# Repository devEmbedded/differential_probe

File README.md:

Modular differential probe (DEDP-100)
=====================================

This repository contains the design files of a 100 MHz differential probe
for use with oscilloscopes. The design is modular and consists of a base
amplifier unit with exchangeable probe tip accessories. The accessory can
be chosen to fit the desired voltage range and connection type.

Currently this project is still in development. While the prototype revisions
work well, they are still being redesigned for improvements.

Files
=====

* [Design notes](design_notes/design_notes.md)
* [Schematics](diff_probe_amplifier/images/diff_probe_amplifier.pdf)
* [User manual](user_manual/DEDP-100_User_Manual.pdf)

License
=======

The design files in this repository are available under CC-BY-SA 3.0 license.

Commercial reproduction of this design is allowed, but the devEmbedded trademark
must not be used to advertise third-party products. Attribution must be included
in documentation or marketing materials.

Suggested format for attribution:

> This device is based on an open source design: https://github.com/devEmbedded/differential_probe

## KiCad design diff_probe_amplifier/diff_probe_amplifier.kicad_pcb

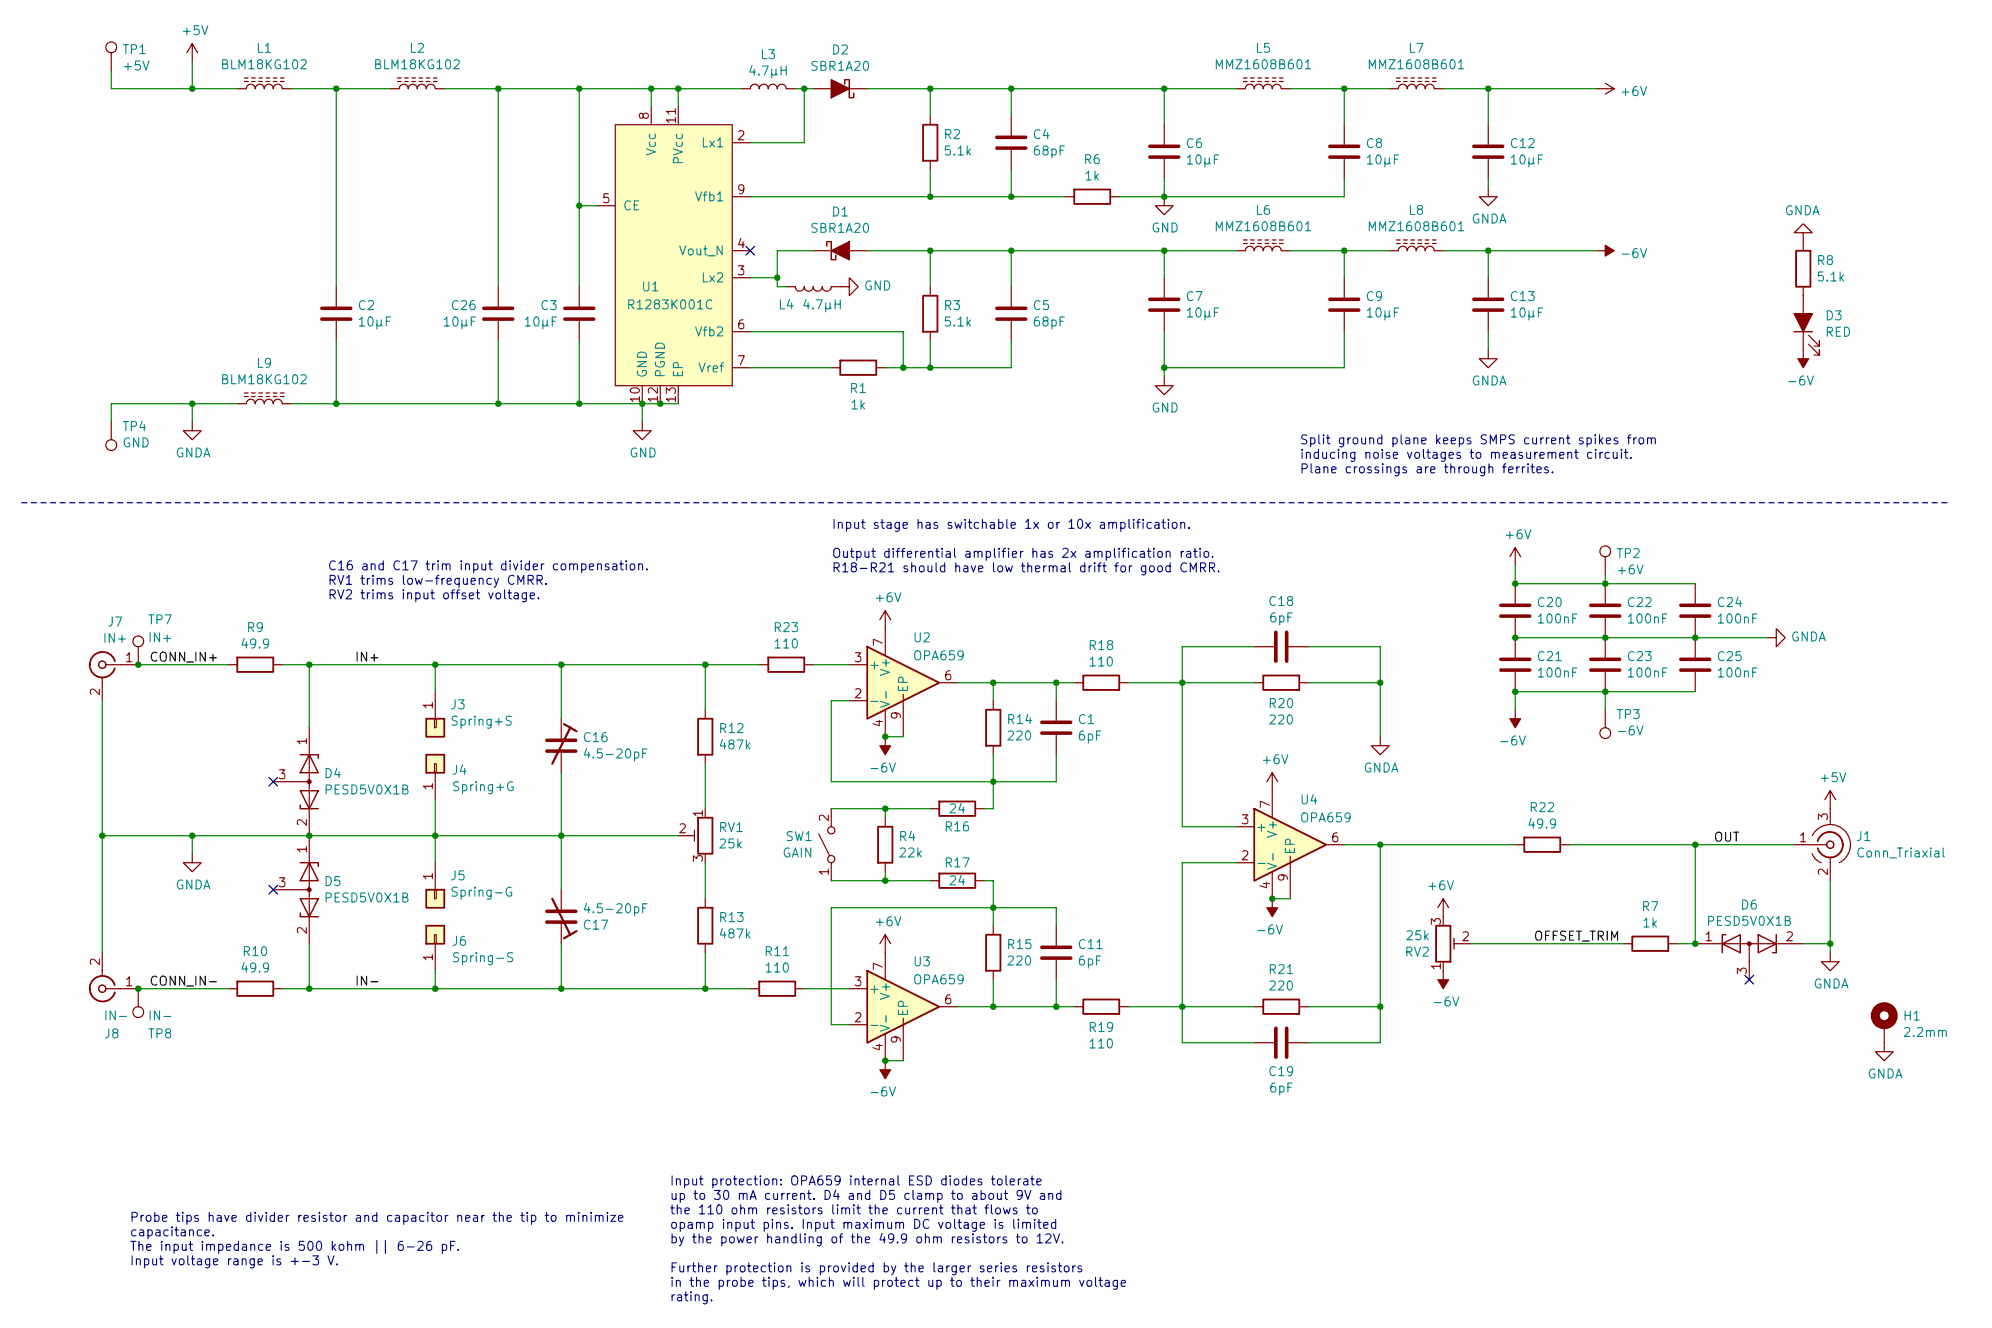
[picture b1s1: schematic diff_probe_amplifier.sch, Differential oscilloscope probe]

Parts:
C1, C11, C18, C19: 6pF; C_0603_1608Metric
C2, C3, C6, C7, C8, C9, C12, C13, C26: 10µF; C_0603_1608Metric; Mfg Part No 0603ZD106KAT2A
C4, C5: 68pF; C_0603_1608Metric; Mfg Part No CML0603C0G101JT50V
C16, C17: 4.5-20pF; C_Trimmer_Knowles_JZ_JR; Mfg Part No JZ200
C20, C21, C22, C23, C24, C25: 100nF; C_0603_1608Metric
D1, D2: SBR1A20; D_SOD-523; Mfg Part No SBR1A20
D3: RED; LED_0603_1608Metric; Mfg Part No QBLP601D-R
D4, D5, D6: PESD5V0X1B; SOT-23
H1: 2.2mm; MountingHole_2.2mm_M2_DIN965_Pad
J1: Conn_Triaxial; TRIAX_SOLDER
J3: Spring+S; TE_2306454_RIGHT; Mfg Part No 2306454-3
J4: Spring+G; TE_2306454_RIGHT; Mfg Part No 2306454-3
J5: Spring-G; TE_2306454_LEFT; Mfg Part No 2306454-3
J6: Spring-S; TE_2306454_LEFT; Mfg Part No 2306454-3
J7: IN+; MMCX_Molex_73415-0961_Horizontal_1.6mm-PCB; Mfg Part No 0734150963
J8: IN-; MMCX_Molex_73415-0961_Horizontal_1.6mm-PCB; Mfg Part No 0734150963
L1, L2, L9: BLM18KG102; L_0603_1608Metric
L3, L4: 4.7µH; L_0805_2012Metric_Pad1.15x1.40mm_HandSolder; Mfg Part No DFE201612E-4R7M=P2
L5, L6, L7, L8: MMZ1608B601; L_0603_1608Metric
R1, R6, R7: 1k; R_0603_1608Metric
R2, R3, R8: 5.1k; R_0603_1608Metric
R4: 22k; R_0603_1608Metric; Mfg Part No ERA-3AED111V
R9, R10, R22: 49.9; R_0603_1608Metric
R11, R23: 110; R_0603_1608Metric
R12, R13: 487k; R_0603_1608Metric
R14, R15, R20, R21: 220; R_0603_1608Metric; Mfg Part No ERA-3AED221V
R16, R17: 24; R_0603_1608Metric
R18, R19: 110; R_0603_1608Metric; Mfg Part No ERA-3AED111V
RV1, RV2: 25k; Potentiometer_Bourns_3314J_Vertical; Mfg Part No 3314J-1-253E
SW1: GAIN; JS202011JCQN; Mfg Part No JS202011JCQN
TP1: +5V; TestPoint_Pad_D2.5mm
TP2: +6V; TestPoint_Pad_D2.5mm
TP3: -6V; TestPoint_Pad_D2.5mm
TP4: GND; TestPoint_Pad_D2.5mm
TP7: IN+; TestPoint_Pad_D2.5mm
TP8: IN-; TestPoint_Pad_D2.5mm
U1: R1283K001C; DFN-12-1EP_3x4mm_P0.5mm_EP1.7x3.3mm
U2, U3, U4: OPA659; Texas_S-PVSON-N8_ThermalVias

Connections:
+5V: J1.3, L1.1, TP1.1
+6V: C12.1, C20.1, C22.1, C24.1, L7.2, RV2.3, TP2.1, U2.7 (V+), U3.7 (V+), U4.7 (V+)
-6V: C13.1, C21.2, C23.2, C25.2, D3.1 (K), L8.2, RV2.1, TP3.1, U2.4 (V-), U2.9 (EP), U3.4 (V-), U3.9 (EP), U4.4 (V-), U4.9 (EP)
/CONN_IN+: J7.1 (In), R9.2, TP7.1
/CONN_IN-: J8.1 (In), R10.2, TP8.1
/IN+: C16.1, D4.1 (K), J3.1, R9.1, R12.1, R23.2
/IN-: C17.1, D5.2 (K), J6.1, R10.1, R11.2, R13.1
/OFFSET_TRIM: R7.1, RV2.2
/OUT: D6.1 (K), J1.1 (In), R7.2, R22.1
GND: C2.2, C3.2, C6.2, C7.2, C8.2, C9.2, C26.2, L4.1, L9.2, R6.1, U1.10 (GND), U1.12 (PGND), U1.13 (EP)
GNDA: C12.2, C13.2, C16.2, C17.2, C18.1, C20.2, C21.1, C22.2, C23.1, C24.2, C25.1, D4.2 (K), D5.1 (K), D6.2 (K), H1.1, J1.2 (Ext), J4.1, J5.1, J7.2 (Ext), J8.2 (Ext), L9.1, R8.2, R20.2, RV1.2, TP4.1
unnamed: C1.1, R14.2, R16.1, U2.2 (-)
unnamed: C1.2, R14.1, R18.1, U2.6
unnamed: C2.1, L1.2, L2.1
unnamed: C4.1, C6.1, D2.1 (K), L5.1, R2.1
unnamed: C4.2, R2.2, R6.2, U1.9 (Vfb1)
unnamed: C5.1, C7.1, D1.2 (A), L6.1, R3.1
unnamed: C5.2, R1.1, R3.2, U1.6 (Vfb2)
unnamed: C8.1, L5.2, L7.1
unnamed: C9.1, L6.2, L8.1
unnamed: C11.1, R15.2, R19.1, U3.6
unnamed: C11.2, R15.1, R17.1, U3.2 (-)
unnamed: C18.2, R18.2, R20.1, U4.3 (+)
unnamed: C19.1, R21.2, R22.2, U4.6
unnamed: C19.2, R19.2, R21.1, U4.2 (-)
unnamed: C3.1, C26.1, L2.2, L3.1, U1.5 (CE), U1.8 (Vcc), U1.11 (PVcc)
unnamed: D1.1 (K), L4.2, U1.3 (Lx2)
unnamed: D2.2 (A), L3.2, U1.2 (Lx1)
unnamed: D3.2 (A), R8.1
unnamed: R1.2, U1.7 (Vref)
unnamed: R11.1, U3.3 (+)
unnamed: R12.2, RV1.1
unnamed: R13.2, RV1.3
unnamed: R4.1, R16.2, SW1.2 (B)
unnamed: R4.2, R17.2, SW1.1 (A)
unnamed: R23.1, U2.3 (+)

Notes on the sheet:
C16 and C17 trim input divider compensation. RV1 trims low-frequency CMRR. RV2 trims input offset voltage.
Input stage has switchable 1x or 10x amplification. Output differential amplifier has 2x amplification ratio. R18-R21 should have low thermal drift for good CMRR.
Probe tips have divider resistor and capacitor near the tip to minimize capacitance. The input impedance is 500 kohm || 6-26 pF. Input voltage range is +-3 V.
Input protection: OPA659 internal ESD diodes tolerate up to 30 mA current. D4 and D5 clamp to about 9V and the 110 ohm resistors limit the current that flows to opamp input pins. Input maximum DC voltage is limited by the power handling of the 49.9 ohm resistors to 12V. Further protection is provid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
Split ground plane keeps SMPS current spikes from inducing noise voltages to measurement circuit. Plane crossings are through ferrites.

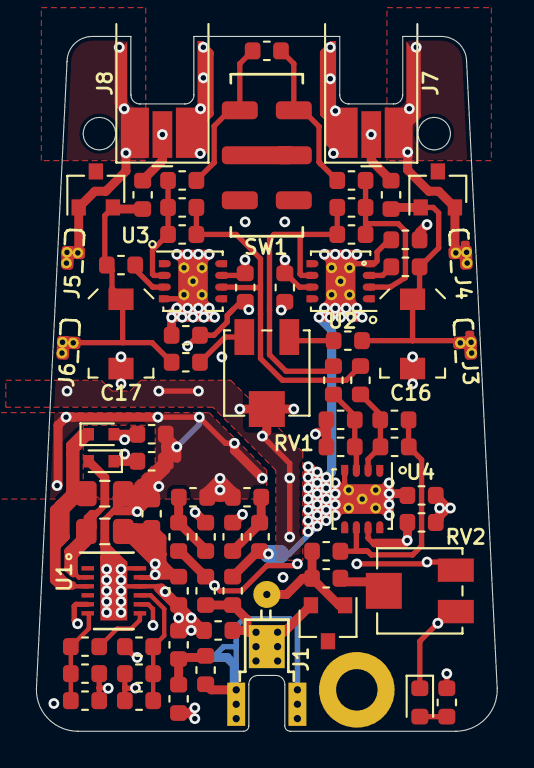
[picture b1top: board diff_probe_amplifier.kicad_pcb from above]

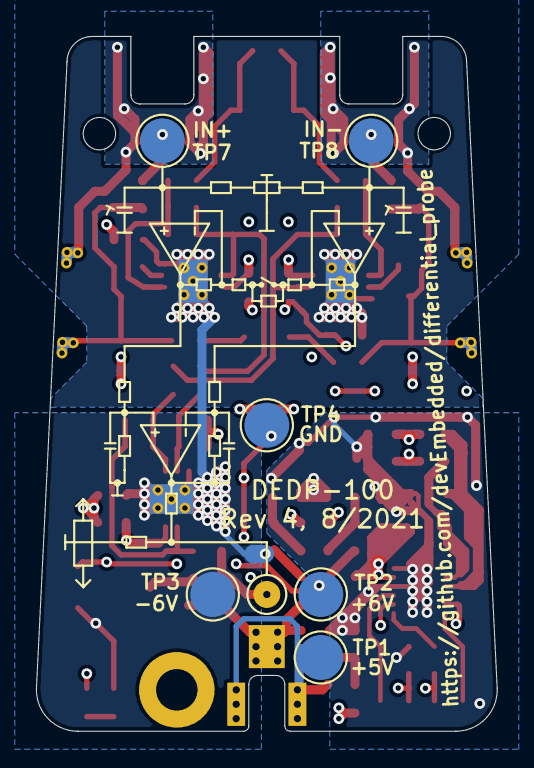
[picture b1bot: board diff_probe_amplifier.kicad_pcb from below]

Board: 4 copper layers, 25.6 x 38.6 mm, 83 parts (6 on the bottom side), 36 nets.

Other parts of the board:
H2, H2#2: HOLE_1.8mm

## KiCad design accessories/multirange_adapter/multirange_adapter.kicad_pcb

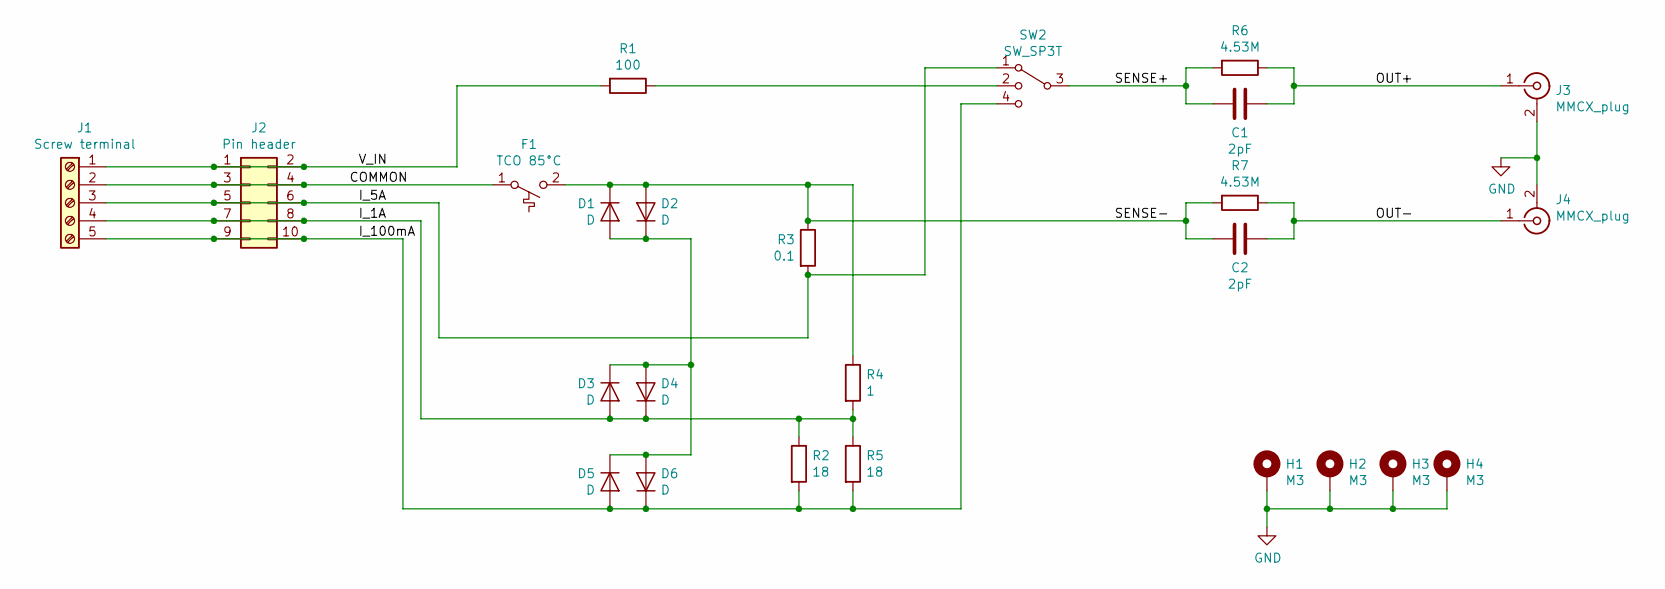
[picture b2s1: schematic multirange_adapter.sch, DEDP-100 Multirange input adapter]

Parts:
C1, C2: 2pF; C_0603_1608Metric
D1, D2, D3, D4, D5, D6: D; D_SMA
F1: TCO 85°C; SA82SB0
H1, H2, H3, H4: M3; MountingHole_3.2mm_M3_ISO14580_Pad
J1: Screw terminal; TerminalBlock_bornier-5_P5.08mm
J2: Pin header; PinHeader_2x05_P2.54mm_Vertical_SMD
J3, J4: MMCX_plug; MMCX_Molex_73415-0961_Horizontal_1.6mm-PCB
R1: 100; R_0603_1608Metric
R2, R5: 18; R_1206_3216Metric
R3: 0.1; R_2512_6332Metric
R4: 1; R_2512_6332Metric
R6, R7: 4.53M; R_0603_1608Metric
SW2: SW_SP3T; JS203011SCQN

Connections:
/COMMON: F1.1 (A), J1.2, J2.3, J2.4
/I_1A: D3.2 (A), D4.1 (K), J1.4, J2.7, J2.8, R2.1, R4.2, R5.1
/I_5A: J1.3, J2.5, J2.6, R3.2, SW2.1
/I_100mA: D5.2 (A), D6.1 (K), J1.5, J2.9, J2.10, R2.2, R5.2, SW2.4
/OUT+: C1.1, J3.1 (In), R6.1
/OUT-: C2.1, J4.1 (In), R7.1
/SENSE+: C1.2, R6.2, SW2.3
/SENSE-: C2.2, D1.1 (K), D2.2 (A), F1.2 (B), R3.1, R4.1, R7.2
/V_IN: J1.1, J2.1, J2.2, R1.2
GND: H1.1, H2.1, H3.1, H4.1, J3.2 (Ext), J4.2 (Ext)
unnamed: D1.2 (A), D2.1 (K), D3.1 (K), D4.2 (A), D5.1 (K), D6.2 (A)
unnamed: R1.1, SW2.2

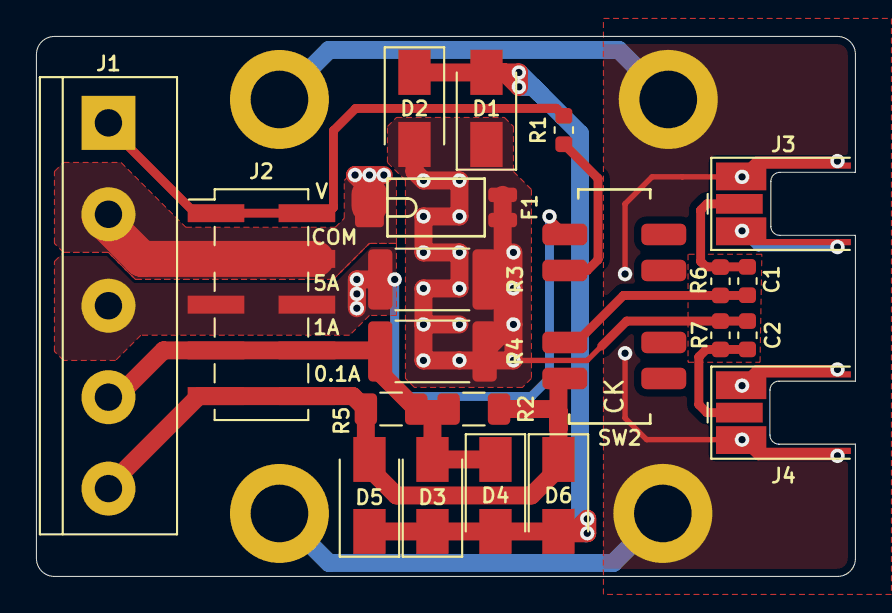
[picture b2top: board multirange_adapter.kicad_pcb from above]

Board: 2 copper layers, 45.5 x 30.0 mm, 25 parts (0 on the bottom side), 12 nets.

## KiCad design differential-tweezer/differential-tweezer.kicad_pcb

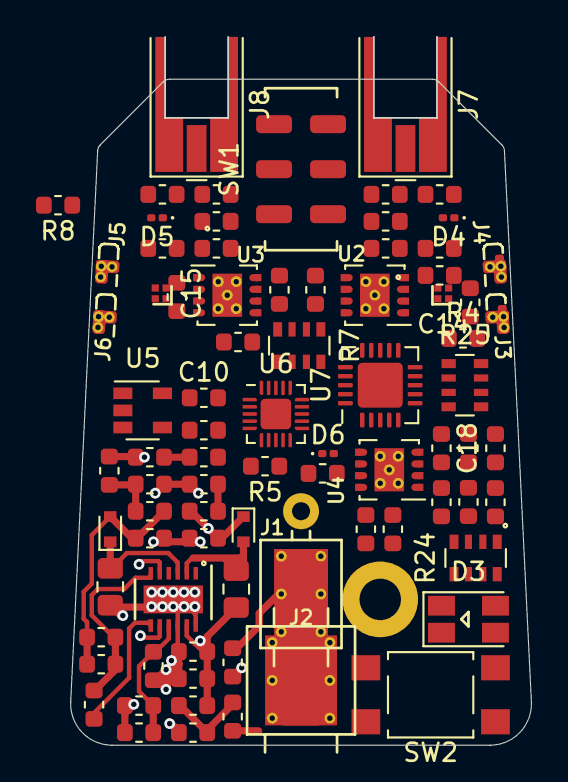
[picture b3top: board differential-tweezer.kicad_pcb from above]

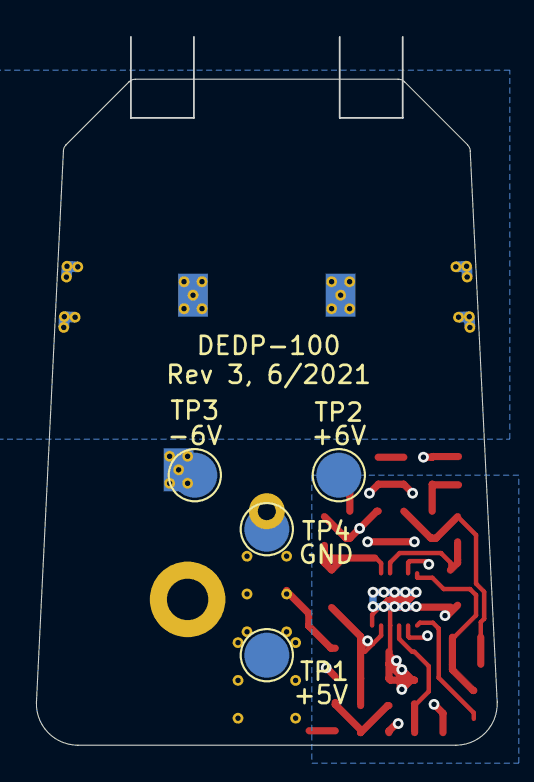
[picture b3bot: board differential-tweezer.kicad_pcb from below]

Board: 4 copper layers, 25.6 x 39.3 mm, 86 parts (4 on the bottom side), 48 nets.

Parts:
C1, C11, C18, C19: 6pF; C_0603_1608Metric
C2, C3, C6, C7, C8, C9, C10, C12, C13, C26: 10µF; C_0603_1608Metric
C4, C5: 68pF; C_0603_1608Metric
C14, C15: LXRW
C20, C21, C22, C23, C24, C25: 100nF; C_0603_1608Metric
D1, D2: NSR05T30; D_SOD-523
D3: APBD3224
D4, D5, D6: PESD5V0H1BSF; D_0201_0603Metric
H1: 2.2mm; MountingHole_2.2mm_M2_DIN965_Pad
J1: Triax_inner; COAX_2MM
J2: Triax_outer; TRIAX_OUTER_3MM
J3: Spring+S; TE_2306454_RIGHT
J4: Spring+G; TE_2306454_RIGHT
J5: Spring-G; TE_2306454_LEFT
J6: Spring-S; TE_2306454_LEFT
J7: IN+; MMCX_Molex_73415-0961_Horizontal_1.6mm-PCB
J8: IN-; MMCX_Molex_73415-0961_Horizontal_1.6mm-PCB
L1, L2, L5, L6, L7, L8, L9: MMZ1608B601; L_0603_1608Metric
L3, L4: 4.7µH; L_0805_2012Metric_Pad1.15x1.40mm_HandSolder
R1, R6: 1k; R_0603_1608Metric
R2, R3, R4, R5: 5.1k; R_0603_1608Metric
R7, R24, R25: 6.8k; R_Array_Convex_4x0603
R8: 30k; R_0603_1608Metric
R9, R10, R22: 49.9; R_0603_1608Metric
R11, R18, R19, R23: 110; R_0603_1608Metric
R12, R13: 487k; R_0603_1608Metric
R14, R15, R20, R21: 220; R_0603_1608Metric
R16, R17: 24; R_0603_1608Metric
SW1: GAIN; JS202011JCQN
SW2: Calibrate; SW_SPST_TL3305A
TP1: +5V; TestPoint_Pad_D2.5mm
TP2: +6V; TestPoint_Pad_D2.5mm
TP3: -6V; TestPoint_Pad_D2.5mm
TP4: GND; TestPoint_Pad_D2.5mm
U1: R1283K001C; DFN-12-1EP_3x4mm_P0.5mm_EP1.7x3.3mm
U2, U3, U4: OPA659; Texas_S-PVSON-N8_ThermalVias
U5: MIC5225-5.0YM5; SOT-23-5
U6: ATtiny826-M; VQFN-20-1EP_3x3mm_P0.4mm_EP1.7x1.7mm
U7: MCP4451; QFN-20-1EP_4x4mm_P0.5mm_EP2.5x2.5mm

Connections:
+5V: J2.1, L1.1, TP1.1
+5VA: C10.1, R4.2, R5.2, R24.6, R24.8, U5.5, U6.4, U7.7, U7.15
+6V: C12.1, C20.1, C22.1, C24.1, L7.2, TP2.1, U2.7, U3.7, U4.7, U5.1, U5.3
-6V: C13.1, C21.2, C23.2, C25.2, L8.2, TP3.1, U2.4, U2.9, U3.4, U3.9, U4.4, U4.9
/AC_COMP+: C14.2, U7.10
/AC_COMP-: C15.2, U7.20
/ADC_NEG: R24.3, R24.4
/ADC_POS: R24.1, R24.7
/CONN_IN+: J7.1, R9.2
/CONN_IN-: J8.1, R10.2
/DC_CMRR1: R7.7, U7.18
/DC_CMRR2: R7.2, R7.8, U7.16
/IN+: C14.3, D4.1, J3.1, R9.1, R12.1, R23.2
/IN-: C15.3, D5.2, J6.1, R10.1, R11.2, R13.1
/OFFSET_TRIM1: R25.1, U7.8
/OFFSET_TRIM2: R25.2, U7.6
/OUT: D6.1, J1.1, R22.1
/SCL: U6.14, U7.3
/SDA: U6.13, U7.4
GND: C2.2, C3.2, C6.2, C7.2, C8.2, C9.2, C26.2, L4.1, L9.2, R6.1, U1.10, U1.12, U1.13
GNDA: C10.2, C12.2, C13.2, C14.1, C14.4, C15.1, C15.4, C18.1, C20.2, C21.1, C22.2, C23.1, C24.2, C25.1, D4.2, D5.1, D6.2, H1.1, J1.2, J4.1, J5.1, J7.2, J8.2, L9.1, R7.6, R20.2, SW1.5, TP4.1, U5.2, U6.3, U6.21, U7.5, U7.11, U7.17, U7.19, U7.21
unnamed: C1.1, R8.1, R14.2, R16.1, U2.2
unnamed: C1.2, R14.1, R18.1, R24.2, U2.6
unnamed: C2.1, L1.2, L2.1
unnamed: C4.1, C6.1, D2.1, L5.1, R2.1
unnamed: C4.2, R2.2, R6.2, U1.9
unnamed: C5.1, C7.1, D1.2, L6.1, R3.1
unnamed: C5.2, R1.1, R3.2, U1.6
unnamed: C8.1, L5.2, L7.1
unnamed: C9.1, L6.2, L8.1
unnamed: C11.1, R15.2, R19.1, R24.5, U3.6
unnamed: C11.2, R8.2, R15.1, R17.1, U3.2
unnamed: C18.2, R18.2, R20.1, R25.8, U4.3
unnamed: C19.1, R21.2, R22.2, R25.6, U4.6
unnamed: C19.2, R19.2, R21.1, R25.7, U4.2
unnamed: C3.1, C26.1, L2.2, L3.1, U1.5, U1.8, U1.11
unnamed: D1.1, L4.2, U1.3
unnamed: D2.2, L3.2, U1.2
unnamed: R1.2, U1.7
unnamed: R4.1, U7.9
unnamed: R5.1, U7.1
unnamed: R7.3, R7.5
unnamed: R11.1, U3.3
unnamed: R7.1, R12.2
unnamed: R7.4, R13.2
unnamed: R16.2, SW1.3
unnamed: R17.2, SW1.2
unnamed: R23.1, U2.3

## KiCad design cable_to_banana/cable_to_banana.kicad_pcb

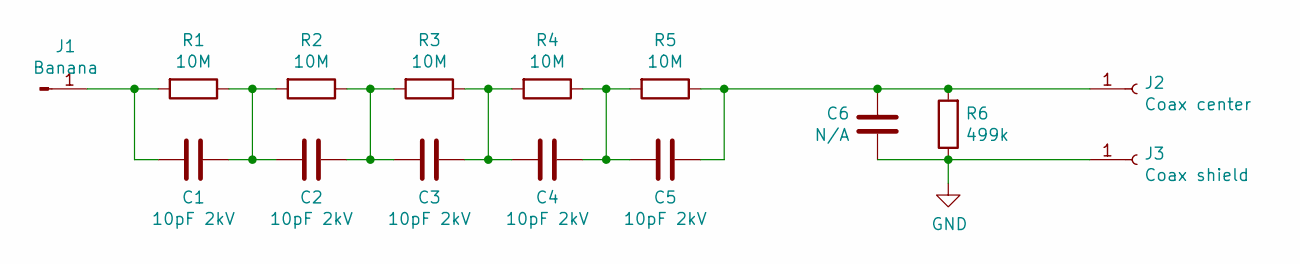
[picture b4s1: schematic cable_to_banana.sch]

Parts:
C1, C2, C3, C4, C5: 10pF 2kV; Minimal1206
C6: N/A; C_0603_1608Metric
J1: Banana; PinHeader_1x01_P2.54mm_Horizontal
J2: Coax center; SIMPLE_PAD
J3: Coax shield; SIMPLE_PAD
R1, R2, R3, R4, R5: 10M; Minimal1206
R6: 499k; R_0603_1608Metric

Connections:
GND: C6.1, J3.1, R6.1
unnamed: C1.1, C2.2, R1.1, R2.2
unnamed: C1.2, J1.1, R1.2
unnamed: C2.1, C3.2, R2.1, R3.2
unnamed: C3.1, C4.2, R3.1, R4.2
unnamed: C4.1, C5.2, R4.1, R5.2
unnamed: C5.1, C6.2, J2.1, R5.1, R6.2

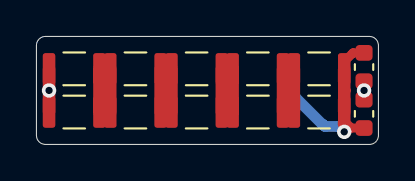
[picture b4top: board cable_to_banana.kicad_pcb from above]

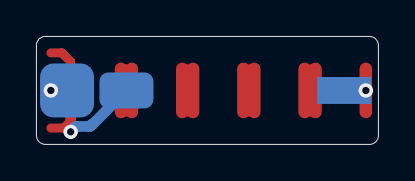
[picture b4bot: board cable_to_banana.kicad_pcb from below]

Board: 2 copper layers, 19.0 x 6.0 mm, 15 parts (3 on the bottom side), 7 nets.

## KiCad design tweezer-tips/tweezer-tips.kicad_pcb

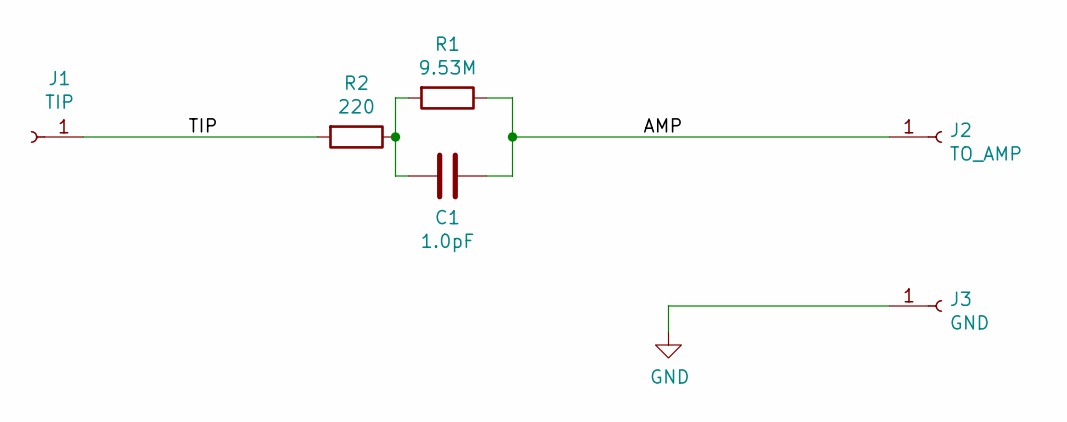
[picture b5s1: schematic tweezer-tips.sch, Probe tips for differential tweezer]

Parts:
C1: 1.0pF; C_0603_1608Metric
J1: TIP; SIMPLE_PAD
J2: TO_AMP; TestPoint_THTPad_D1.0mm_Drill0.5mm
J3: GND; SIMPLE_PAD
R1: 9.53M; R_0603_1608Metric
R2: 220; R_0603_1608Metric

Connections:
/AMP: C1.2, J2.1, R1.1
/TIP: J1.1, R2.2
GND: J3.1
unnamed: C1.1, R1.2, R2.1

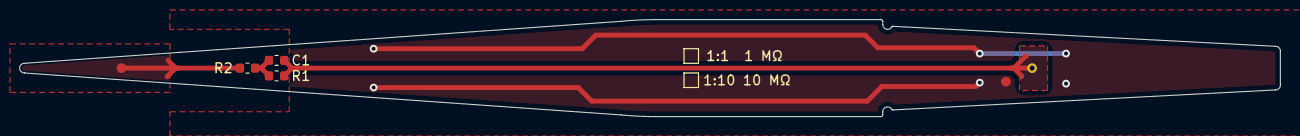
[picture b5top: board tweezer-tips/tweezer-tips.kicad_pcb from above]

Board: 2 copper layers, 130.0 x 10.0 mm, 6 parts (0 on the bottom side), 3 nets.

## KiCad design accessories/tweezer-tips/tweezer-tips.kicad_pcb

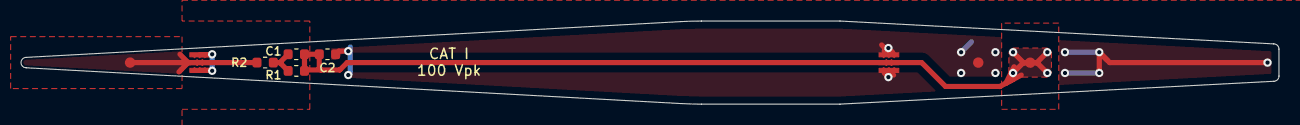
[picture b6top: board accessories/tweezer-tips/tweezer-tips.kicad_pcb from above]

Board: 2 copper layers, 121.1 x 8.0 mm, 9 parts (0 on the bottom side), 4 nets.

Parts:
C1: 1.0pF; C_0603_1608Metric
C2: N/A; C_0603_1608Metric
E1, E2: SPARK_GAP; PCB_SPARK_GAP
J1: TIP; SIMPLE_PAD
J2: TO_AMP; SIMPLE_PAD
J3: GND; SIMPLE_PAD
R1: 9.53M; R_0603_1608Metric
R2: 220; R_0603_1608Metric

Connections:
/AMP: C1.2, C2.1, E2.1, J2.1, R1.1
/TIP: E1.1, J1.1, R2.2
GND: C2.2, E1.2, E2.2, J3.1
unnamed: C1.1, R1.2, R2.1

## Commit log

2021-01-13 First revision
2021-05-11 Revision 2
2021-06-04 Revision 3
2021-06-22 BOM updates
2021-08-04 Beginnings of manual
2021-08-05 Reorganize repository
2021-08-09 Debugging noise issues in rev3
2021-08-18 Design notes about input resonances
2021-08-23 Revision 4
2021-08-23 Small adjustment to PCB edges after JLCPCB review failed
2021-09-01 Update enclosure to match new PCB design
2021-09-10 Design notes on rev4 testing
